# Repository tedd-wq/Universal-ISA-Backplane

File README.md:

# Universal ISA Backplane

*Initial layout plan. Bracketed area in the top right is where normal PC I/O goes.*

This backplane is initially intended to be used with with a [PC/104 compute board](https://en.wikipedia.org/wiki/PC/104) for legacy ISA card applications. It aims to implement the complete 16-bit ISA bus specification in a microATX form factor. In future, the PCI bus could also be implemented, allowing use of PC/104-Plus (ISA and PCI), or PCI/104 (PCI only) compute boards.

This project was based on [spark2k06's Universal ITX Backplane](https://github.com/spark2k06/Universal-ITX-Backplane), but is heavily modified to focus on PC/104 support and in a microATX form factor. More information visit spark2k06's project on their [Hackaday page](https://hackaday.io/project/175340-universal-itx-backplane).

The project is mostly unfinished. No layout exists, most of the schematic is unfinished.

## Specifications

* Standard microATX board
* 2x ISA 8-/16-bit slots (1 shared with PCI slot)
* 3x 32-bit PCI slots (1 shared with ISA slot)
* 1x PC/104, PC/104+, PCI-104 connection
* Compatibility with modern ATX power supplies
* Compatibility with modern ATX computer cases
* Standard ATX I/O shield area with connectors bringing PC/104 connections to the rear of an ATX case

## Reference Documentation
* [IBM, *Personal Computer XT Hardware Technical Reference*, Apr. 1983](https://archive.org/details/IBMPCXTTechnicalReference1502237)
* [Intel, *ATX Multi Rail Desktop Power Supply Design Guide*, Revision 003, Jun. 2020](https://web.archive.org/web/20210222203819/https://d2pgu9s4sfmw1s.buttfront.net/UAM/Prod/Done/a062E00001XMVETQA5/b2f2f54c-e980-7c06-4032-9bd4e037c83b?Expires=1614026599&Key-Pair-Id=APKAJKRNIMMSNYXST6UA&Signature=iVsGBI7emsEdrFsQ67~1S2M90n5TYe3~QRV4TUX1VC-EseakcayGKQeIrDqA~ls21nyFEuSEcp9TwYA2uYXHQRfrjsYAhPvPaKLNivtX25XWNG2Bqr1eajUeZY6SobcaUhqU8I1coBOXz6TzmLMmgRiy4awrNQnBFtagJsJRME50wE8zd8HrBmgITOGB7dXv9IFX3YCMPpx1PXaubRAcfm9tsS71Sn6xf2n2rSizwWA-JjXuYK6sZhXKNNzn-7FtBtRJoyx~uOnWPtvxE2i-O1X1cFFpnhq3wDn1Kubh-qttzKiRYs0pnXElqDpH4i9TFOFBCR-g2dmtm6USEUgBBA__)
* [Intel, *ATX Specification*, Version 2.2, 2004](https://web.archive.org/web/20120725150314/http://www.formfactors.org/developer/specs/atx2_2.pdf)
* [Intel, *ISA Bus Specification and Application Notes*, Revision 2.01, 12 Sep. 1989](https://archive.org/details/bitsavers_intelbusSpep89_3342148/)
* [Intel, *microATX Motherboard Interface Specification*, Version 1.2, 2004](http://www.motherboards.org/files/techspecs/matxspe1.2.pdf)
* [PC/104 Embedded Consortium, *PC/104 Specification*, Version 2.6, 13 Oct. 2008](https://pc104.org/hardware-specifications/pc104/)
* [PC/104 Embedded Consortium, *PC/104-Plus Specification*, Version 2.3, 13 Oct. 2008](https://pc104.org/hardware-specifications/pc104-plus/)
* [Tom Shanley and Don Anderson, *ISA System Architecture*, Third Edition, 1995](https://archive.org/details/ISA_System_Architecture)

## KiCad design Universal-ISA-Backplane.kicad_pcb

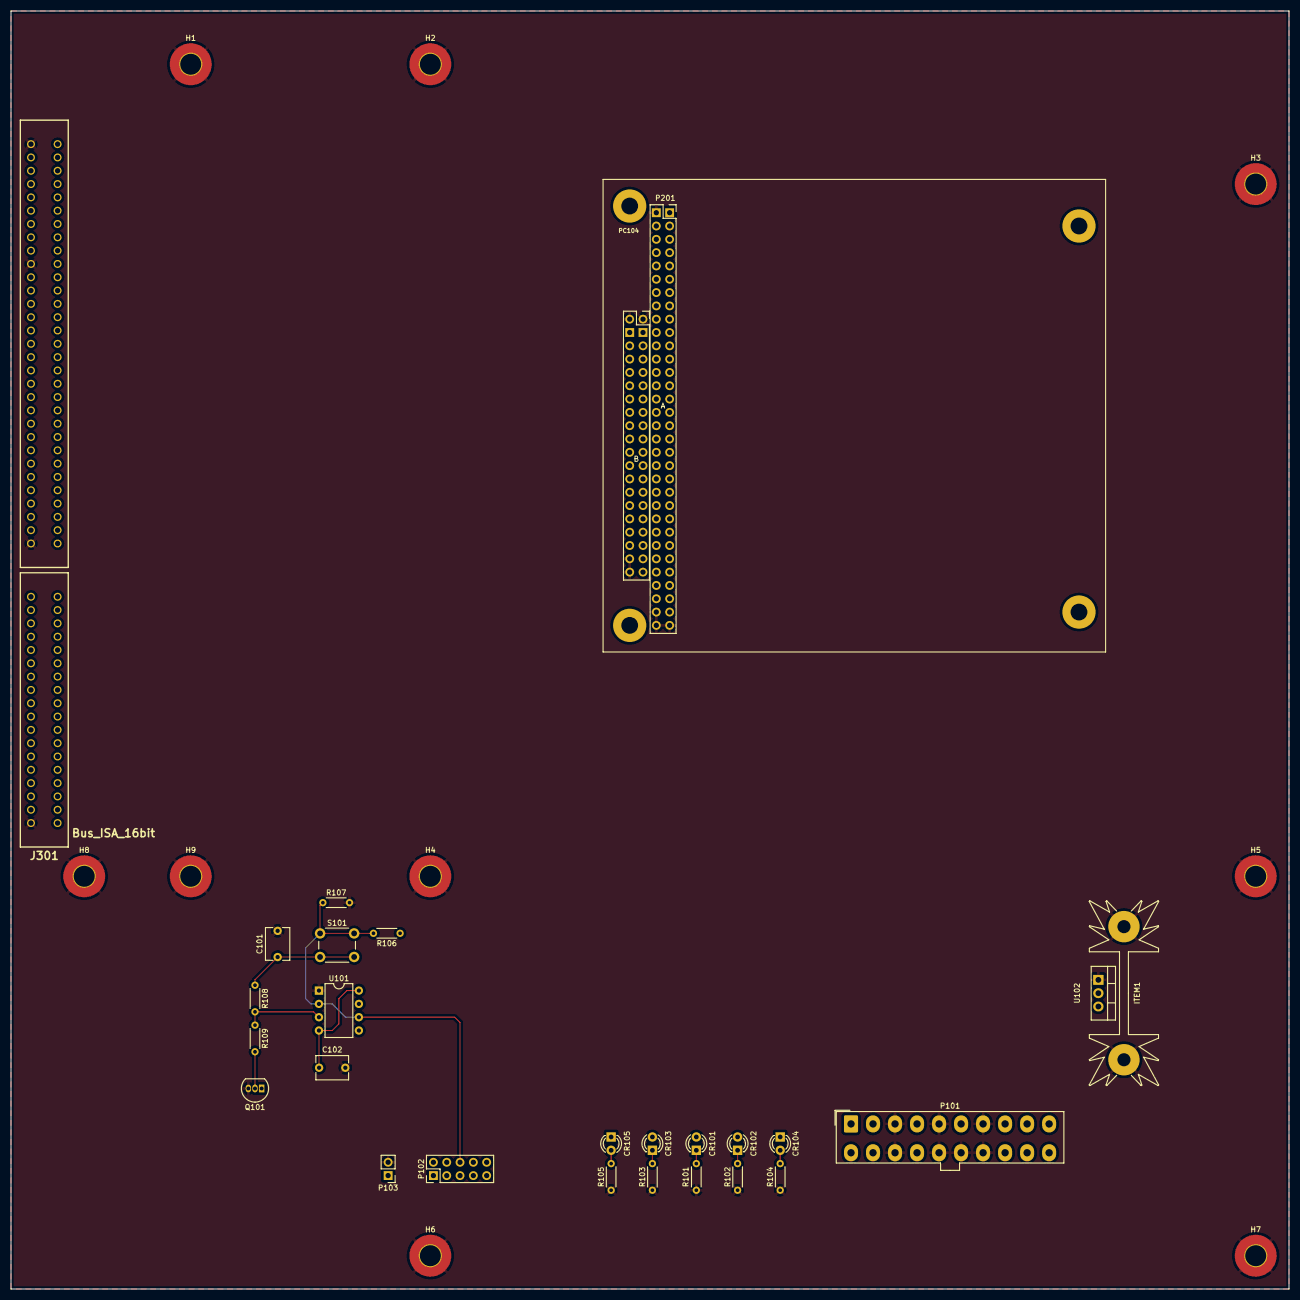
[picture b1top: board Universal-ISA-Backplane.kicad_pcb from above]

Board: 4 copper layers, 243.8 x 243.8 mm, 35 parts (0 on the bottom side), 105 nets.

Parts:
C101: µ47 10% 50V CR X7R; C_Disc_D6.0mm_W4.4mm_P5.00mm
C102: µ1 10% 50V CR X7R; C_Disc_D6.0mm_W4.4mm_P5.00mm
CR101: +5VSB; LED_D3.0mm
CR102: +5V; LED_D3.0mm
CR103: +12V; LED_D3.0mm
CR104: -12V; LED_D3.0mm
CR105: -5V; LED_D3.0mm
H1, H2, H3, H4, H5, H6, H7, H8, H9: MountingHole_Pad; MountingHole_4mm_Pad_TopBottom
ITEM1: Heatsink_Pad; Heatsink_Fischer_SK104-STC-STIC_35x13mm_2xDrill2.5mm
J301: Bus_ISA_16bit; ISA16
P101: ATX 20-Pin Power; Molex_Mini-Fit_Jr_5566-20A_2x10_P4.20mm_Vertical
P102: F_PANEL; PinHeader_2x05_P2.54mm_Vertical
P103: HW_SW_PWR; PinHeader_1x02_P2.54mm_Vertical
P201: PC104; PC104_Platform
Q101: BC547; TO-92_Inline
R101, R102, R105: 270R 10% QW MF; R_Axial_DIN0204_L3.6mm_D1.6mm_P5.08mm_Horizontal
R103, R104: 1K 10% QW MF; R_Axial_DIN0204_L3.6mm_D1.6mm_P5.08mm_Horizontal
R106, R107, R109: 100K 10% QW MF; R_Axial_DIN0204_L3.6mm_D1.6mm_P5.08mm_Horizontal
R108: 270K 10% QW MF; R_Axial_DIN0204_L3.6mm_D1.6mm_P5.08mm_Horizontal
S101: Power; SW_PUSH_6mm
U101: 555; DIP-8_W7.62mm
U102: 7905; TO-220-3_Vertical

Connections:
/ISA1/+5V: CR102.2 (A), J301.B3 (+5V), J301.B29 (VCC), J301.D16 (+5V), P101.4 (+5V), P101.6 (+5V), P101.19 (+5V), P101.20 (+5V), P201.B3 (+5V), P201.B29 (+5V), P201.D16 (+5V)
/ISA1/+12V: CR103.2 (A), J301.B9 (+12V), P101.10 (+12V), P201.B9 (+12V)
/ISA1/-5V: CR105.1 (K), J301.B5 (-5V), P201.B5 (-5V), U102.3 (VO)
/ISA1/-12V: CR104.1 (K), J301.B7 (-12V), P101.12 (-12V), P201.B7 (-12V), U102.2 (VI)
/ISA1/AEN: J301.A11 (AEN), P201.A11 (AEN)
/ISA1/BALE: J301.B28 (ALE), P201.B28 (BALE)
/ISA1/BCLK: J301.B20 (CLK), P201.B20 (BCLK)
/ISA1/DRQ0: J301.D9 (DRQ0), P201.D9 (DRQ0)
/ISA1/DRQ1: J301.B18 (DRQ1), P201.B18 (DRQ1)
/ISA1/DRQ2: J301.B6 (DRQ2), P201.B6 (DRQ2)
/ISA1/DRQ3: J301.B16 (DRQ3), P201.B16 (DRQ3)
/ISA1/DRQ5: J301.D11 (DRQ5), P201.D11 (DRQ5)
/ISA1/DRQ6: J301.D13 (DRQ6), P201.D13 (DRQ6)
/ISA1/DRQ7: J301.D15 (DRQ7), P201.D15 (DRQ7)
/ISA1/IOCHRDY: J301.A10 (~IOCHRDY), P201.A10 (IOCHRDY)
/ISA1/IRQ3: J301.B25 (IRQ3), P201.B25 (IRQ3)
/ISA1/IRQ4: J301.B24 (IRQ4), P201.B24 (IRQ4)
/ISA1/IRQ5: J301.B23 (IRQ5), P201.B23 (IRQ5)
/ISA1/IRQ6: J301.B22 (IRQ6), P201.B22 (IRQ6)
/ISA1/IRQ7: J301.B21 (IRQ7), P201.B21 (IRQ7)
/ISA1/IRQ9: J301.B4 (IRQ9), P201.B4 (IRQ9)
/ISA1/IRQ10: J301.D3 (IRQ10), P201.D3 (IRQ10)
/ISA1/IRQ11: J301.D4 (IRQ11), P201.D4 (IRQ11)
/ISA1/IRQ12: J301.D5 (IRQ12), P201.D5 (IRQ12)
/ISA1/IRQ14: J301.D7 (IRQ14), P201.D7 (IRQ14)
/ISA1/IRQ15: J301.D6 (IRQ15), P201.D6 (IRQ15)
/ISA1/LA17: J301.C8 (LA17), P201.C8 (LA17)
/ISA1/LA18: J301.C7 (LA18), P201.C7 (LA18)
/ISA1/LA19: J301.C6 (LA19), P201.C6 (LA19)
/ISA1/LA20: J301.C5 (LA20), P201.C5 (LA20)
/ISA1/LA21: J301.C4 (LA21), P201.C4 (LA21)
/ISA1/LA22: J301.C3 (LA22), P201.C3 (LA22)
/ISA1/LA23: J301.C2 (LA23), P201.C2 (LA23)
/ISA1/OSC: J301.B30 (OSC), P201.B30 (OSC)
/ISA1/RESET: J301.B2 (RESET), P201.B2 (RESET)
/ISA1/SA0: J301.A31 (BA00), P201.A31 (SA0)
/ISA1/SA1: J301.A30 (BA01), P201.A30 (SA1)
/ISA1/SA2: J301.A29 (BA02), P201.A29 (SA2)
/ISA1/SA3: J301.A28 (BA03), P201.A28 (SA3)
/ISA1/SA4: J301.A27 (BA04), P201.A27 (SA4)
/ISA1/SA5: J301.A26 (BA05), P201.A26 (SA5)
/ISA1/SA6: J301.A25 (BA06), P201.A25 (SA6)
/ISA1/SA7: J301.A24 (BA07), P201.A24 (SA7)
/ISA1/SA8: J301.A23 (BA08), P201.A23 (SA8)
/ISA1/SA9: J301.A22 (BA09), P201.A22 (SA9)
/ISA1/SA10: J301.A21 (BA10), P201.A21 (SA10)
/ISA1/SA11: J301.A20 (BA11), P201.A20 (SA11)
/ISA1/SA12: J301.A19 (BA12), P201.A19 (SA12)
/ISA1/SA13: J301.A18 (BA13), P201.A18 (SA13)
/ISA1/SA14: J301.A17 (BA14), P201.A17 (SA14)
/ISA1/SA15: J301.A16 (BA15), P201.A16 (SA15)
/ISA1/SA16: J301.A15 (BA16), P201.A15 (SA16)
/ISA1/SA17: J301.A14 (BA17), P201.A14 (SA17)
/ISA1/SA18: J301.A13 (BA18), P201.A13 (SA18)
/ISA1/SA19: J301.A12 (BA19), P201.A12 (SA19)
/ISA1/SD0: J301.A9 (DB0), P201.A9 (SD0)
/ISA1/SD1: J301.A8 (DB1), P201.A8 (SD1)
/ISA1/SD2: J301.A7 (DB2), P201.A7 (SD2)
/ISA1/SD3: J301.A6 (DB3), P201.A6 (SD3)
/ISA1/SD4: J301.A5 (DB4), P201.A5 (SD4)
/ISA1/SD5: J301.A4 (DB5), P201.A4 (SD5)
/ISA1/SD6: J301.A3 (DB6), P201.A3 (SD6)
/ISA1/SD7: J301.A2 (DB7), P201.A2 (SD7)
/ISA1/SD8: J301.C11 (D8), P201.C11 (SD8)
/ISA1/SD9: J301.C12 (D9), P201.C12 (SD9)
/ISA1/SD10: J301.C13 (D10), P201.C13 (SD10)
/ISA1/SD11: J301.C14 (D11), P201.C14 (SD11)
/ISA1/SD12: J301.C15 (D12), P201.C15 (SD12)
/ISA1/SD13: J301.C16 (D13), P201.C16 (SD13)
/ISA1/SD14: J301.C17 (D14), P201.C17 (SD14)
/ISA1/SD15: J301.C18 (D15), P201.C18 (SD15)
/ISA1/TC: J301.B27 (TC), P201.B27 (TC)
/ISA1/~DACK0: J301.D8 (~DACK0), P201.D8 (~DACK0)
/ISA1/~DACK1: J301.B17 (~DACK1), P201.B17 (~DACK1)
/ISA1/~DACK2: J301.B26 (~DACK2), P201.B26 (~DACK2)
/ISA1/~DACK3: J301.B15 (~DACK3), P201.B15 (~DACK3)
/ISA1/~DACK5: J301.D10 (~DACK5), P201.D10 (~DACK5)
/ISA1/~DACK6: J301.D12 (~DACK6), P201.D12 (~DACK6)
/ISA1/~DACK7: J301.D14 (~DACK7), P201.D14 (~DACK7)
/ISA1/~IOCHK: J301.A1 (~IOCHK), P201.A1 (~IOCHK)
/ISA1/~IOCS16: J301.D2 (~IOCS16), P201.D2 (~IOCS16)
/ISA1/~IOR: J301.B14 (~IOR), P201.B14 (~IOR)
/ISA1/~IOW: J301.B13 (~IOW), P201.B13 (~IOW)
/ISA1/~MASTER: J301.D17 (MASTER), P201.D17 (~MASTER)
/ISA1/~MEMCS16: J301.D1 (~MEMCS16), P201.D1 (~MEMCS16)
/ISA1/~MEMR: J301.C9 (~MEMR), P201.C9 (~MEMR)
/ISA1/~MEMW: J301.C10 (~MEMW), P201.C10 (~MEMW)
/ISA1/~REFRESH: J301.B19 (~REFRESH), P201.B19 (~REFRESH)
/ISA1/~SBHE: J301.C1 (SBHE), P201.C1 (~SBHE)
/ISA1/~SMEMR: J301.B12 (~SMEMR), P201.B12 (~SMEMR)
/ISA1/~SMEMW: J301.B11 (~SMEMW), P201.B11 (~SMEMW)
/ISA1/~SRDY: J301.B8 (~SRDY), P201.B8 (~SRDY)
/Power/+5VSB: C102.1, CR101.2 (A), P101.9 (+5VSB), R106.1, U101.4 (R), U101.8 (VCC)
GND: C101.2, C102.2, H1.1, H2.1, H3.1, H4.1, H5.1, H6.1, H7.1, H8.1, H9.1, ITEM1.1, J301.B1 (GND), J301.B10 (GND), J301.B31 (GND), J301.D18 (GND), P101.3 (GND), P101.5 (GND), P101.7 (GND), P101.13 (GND), P101.15 (GND), P101.16 (GND), P101.17 (GND), P103.2, P201.A32 (GND), P201.B1 (GND), P201.B31 (GND), P201.B32 (GND), P201.C0 (GND), P201.D0 (GND), P201.D18 (GND), P201.D19 (GND), Q101.3 (E), R101.2, R102.1, R103.1, R104.1, R105.1, R107.2, U101.1 (GND), U102.1 (GND)
unnamed: C101.1, P102.8, R108.1, S101.2
unnamed: CR101.1 (K), R101.1
unnamed: CR102.1 (K), R102.2
unnamed: CR103.1 (K), R103.2
unnamed: CR104.2 (A), R104.2
unnamed: CR105.2 (A), R105.2
unnamed: P101.1 (+3.3V), P101.2 (+3.3V), P101.11 (+3.3V)
unnamed: P101.14 (~PS_ON), P103.1, Q101.1 (C)
unnamed: P102.6, R106.2, R107.1, S101.1, U101.2 (TR), U101.6 (THR)
unnamed: Q101.2 (B), R109.2
unnamed: R108.2, R109.1, U101.3 (Q)

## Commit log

2022-01-08 Upgrade to Kicad 6.0
    Upgraded project to Kicad version 6.0.
    Cleaned some DRC errors in layout.
    Swapped base and emitter of Q2 (Fixes bug #1 .
2022-01-29 Splitting schematic to multiple A4 sheets, etc
    * Splitting schematic also involved redrawing the circuit.
    * Redesign ATX power circuit.
    * Refine component specifics (circuit designation, manufacturer PN, tolerance, etc.).
    * Also delete PCB layout for future recreation.
    * Rename to "Universal ISA Backplane" as initial design will be microATX.
    * Fix project symbol libraries (delete unused symbols, rename "*-rescue" to "*-symbols").
2022-01-29 Remove fp-info-cache
2022-01-29 Update README.md
    * Added Github dark-mode image
    * Added Reference Documentation and links
    * Some other minor edits
2022-01-29 Update README.md
    Fixed heading size
2022-04-20 Initial steps for PCB layout
2022-04-21 PC/104 and ISA connector fixes
    And further development
2022-04-21 Kicad resave fixup
2022-04-21 Just another resave
    Not sure why eeschema changed the values and footprints of H1 - H9
2022-04-21 Bigger images

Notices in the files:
Universal-ISA-Backplane.kicad_pcb:
Tedd | License: GFDLv3
